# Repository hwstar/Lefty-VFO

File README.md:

# Lefty-VFO
Lefty Quad output VFO Motherboard

This is a 4 output VFO module for the lefty transceiver.

It uses 2 SI5351/MS5351 clock generator chips. 

There is a 4 channel PCA9546 I2C multiplexer on the board which is used to switch between the two SI5351's since they have a fixed device address.

Each SI5351 is driven from a common 26 MHz TCXO source using 74LVC1G04's as a buffer.

The SI5351's have dedicated ME6211 3.3V regulators to reduce cross coupling of spurs on the 3.3v power rails.

The VFO board used a Weact "Black Pill" STM32 MPU module. This module has 512kB of flash and 128kB of ram.

The display mounts on the front of the board using a 20 pin female socket header. The display used is a 3.3V 12864 monochrome display with SPI bus capability.

The vfo board is powered from 9-15V and uses a 12V to 5V switching power supply module with input PI filter to reduce the noise generated from the switcher module.

There is one 8 pin JST XH connector supplies 12V power and provides access to the I2C bus coming from one of the PCA9546 outputs.

The vfo board supports an optional 4x4 keypad, and an optical encoder.

There are 2 pin connector for the fan output. 

There are 2 pin connectors for the ptt, tune, and s-meter inputs.

There is a 6 pin connector for the UART in the Black pill.

There is an I2C EEPROM on the board to facilitate storing VFO configuration settings

The PCB design was done with KiCAD 6.0. The BOM files are in .csv format and are included in the top level directory. There is a combined BOM, and separate top and bottom SMT BOM's.

The firmware for the VFO is in a separate project located [here] (https://github.com/hwstar/FW_VFO_STM32_BLACK_PILL_ST7920) 

The gerber files are in the directory VFO_Rev_X2_Gerbers.

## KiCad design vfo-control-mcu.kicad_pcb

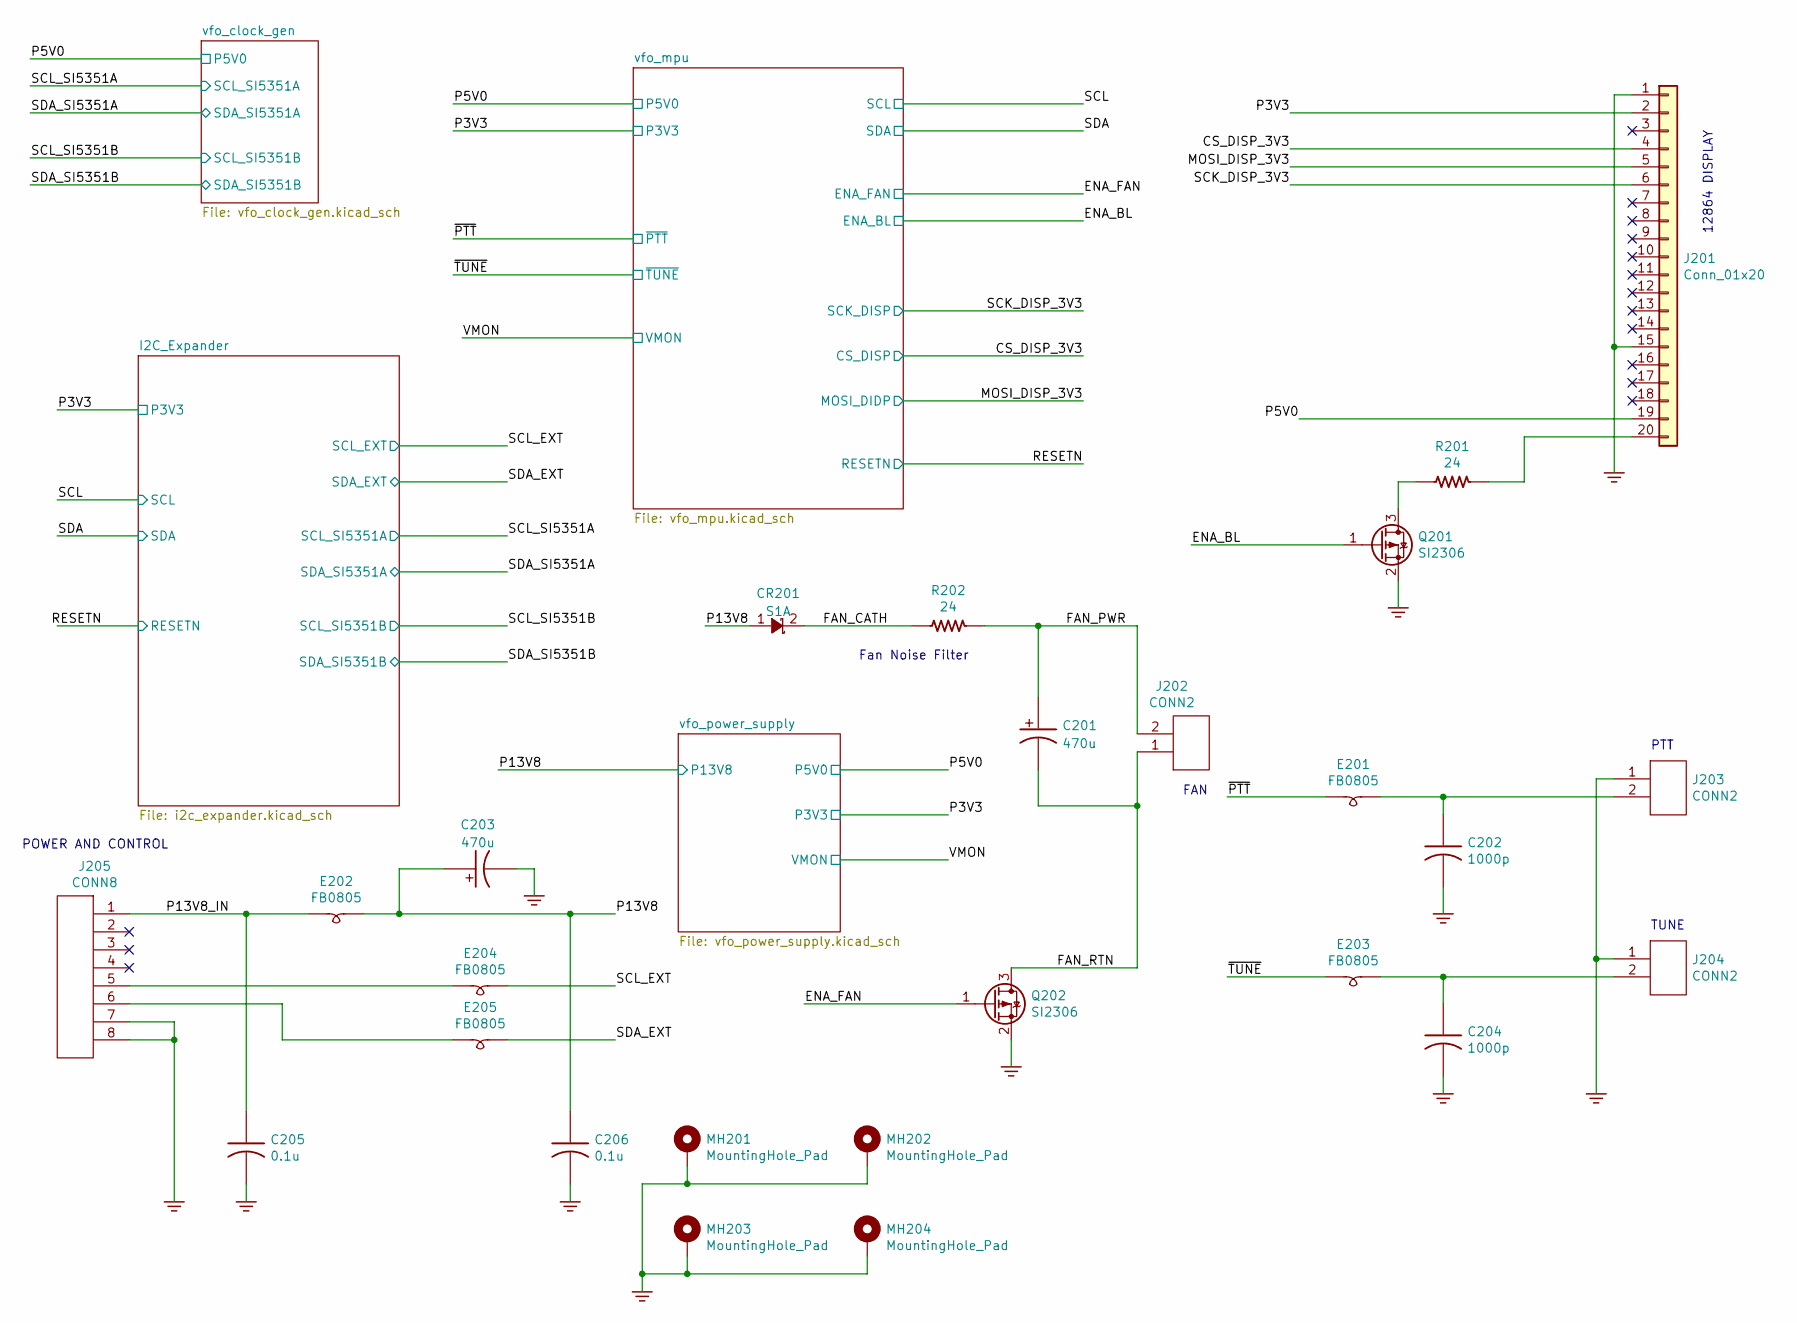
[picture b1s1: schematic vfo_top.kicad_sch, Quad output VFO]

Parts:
C201, C203: 470u; CP_Elec_10x10; PartNumber 800270-477
C202, C204: 1000p; C_0805_2012Metric_Pad1.18x1.45mm_HandSolder; PartNumber 800239-102
C205, C206: 0.1u; C_0805_2012Metric_Pad1.18x1.45mm_HandSolder; PartNumber 800238-104
CR201: S1A; SMA-SAR; PartNumber 800109-101
E201, E202, E203, E204, E205: FB0805; L_0805_2012Metric_Pad1.05x1.20mm_HandSolder; PartNumber 800245-601
J201: Conn_01x20; 12864_display; PartNumber 800283-020
J202, J203, J204: CONN2; JST_B2B_XH_A; PartNumber 800114-102
J205: CONN8; JST_B8B_XH_A; PartNumber 800114-108
MH201, MH202, MH203, MH204: MountingHole_Pad; MountingHole_3.2mm_M3_Pad_Via
Q201, Q202: SI2306; SOT-23; PartNumber 800123-101
R201, R202: 24; R_2512_6332Metric_Pad1.40x3.35mm_HandSolder; PartNumber 800248-240

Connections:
/vfo_top/CS_DISP_3V3: J201.4; also elsewhere on the board
/vfo_top/ENA_BL: Q201.1 (G); also elsewhere on the board
/vfo_top/ENA_FAN: Q202.1 (G); also elsewhere on the board
/vfo_top/FAN_CATH: CR201.2 (K), R202.2
/vfo_top/FAN_PWR: C201.1, J202.2, R202.1
/vfo_top/FAN_RTN: C201.2, J202.1, Q202.3 (D)
/vfo_top/MOSI_DISP_3V3: J201.5; also elsewhere on the board
/vfo_top/P3V3: J201.2; also elsewhere on the board
/vfo_top/P5V0: J201.19; also elsewhere on the board
/vfo_top/P13V8: C203.1, C206.1, CR201.1 (A), E202.2; also elsewhere on the board
/vfo_top/P13V8_IN: C205.1, E202.1, J205.1
/vfo_top/SCK_DISP_3V3: J201.6; also elsewhere on the board
/vfo_top/SCL_EXT: E204.2; also elsewhere on the board
/vfo_top/SDA_EXT: E205.2; also elsewhere on the board
/vfo_top/~PTT: E201.1; also elsewhere on the board
/vfo_top/~TUNE: E203.1; also elsewhere on the board
GND: C202.2, C203.2, C204.2, C205.2, C206.2, J201.1, J201.15, J203.1, J204.1, J205.7, J205.8, MH201.1, MH202.1, MH203.1, MH204.1, Q201.2 (S), Q202.2 (S); also elsewhere on the board
unnamed: C202.1, E201.2, J203.2
unnamed: C204.1, E203.2, J204.2
unnamed: E204.1, J205.5
unnamed: E205.1, J205.6
unnamed: J201.20, R201.1
unnamed: Q201.3 (D), R201.2

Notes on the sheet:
POWER AND CONTROL
PTT
TUNE
12864 DISPLAY
Fan Noise Filter
FAN

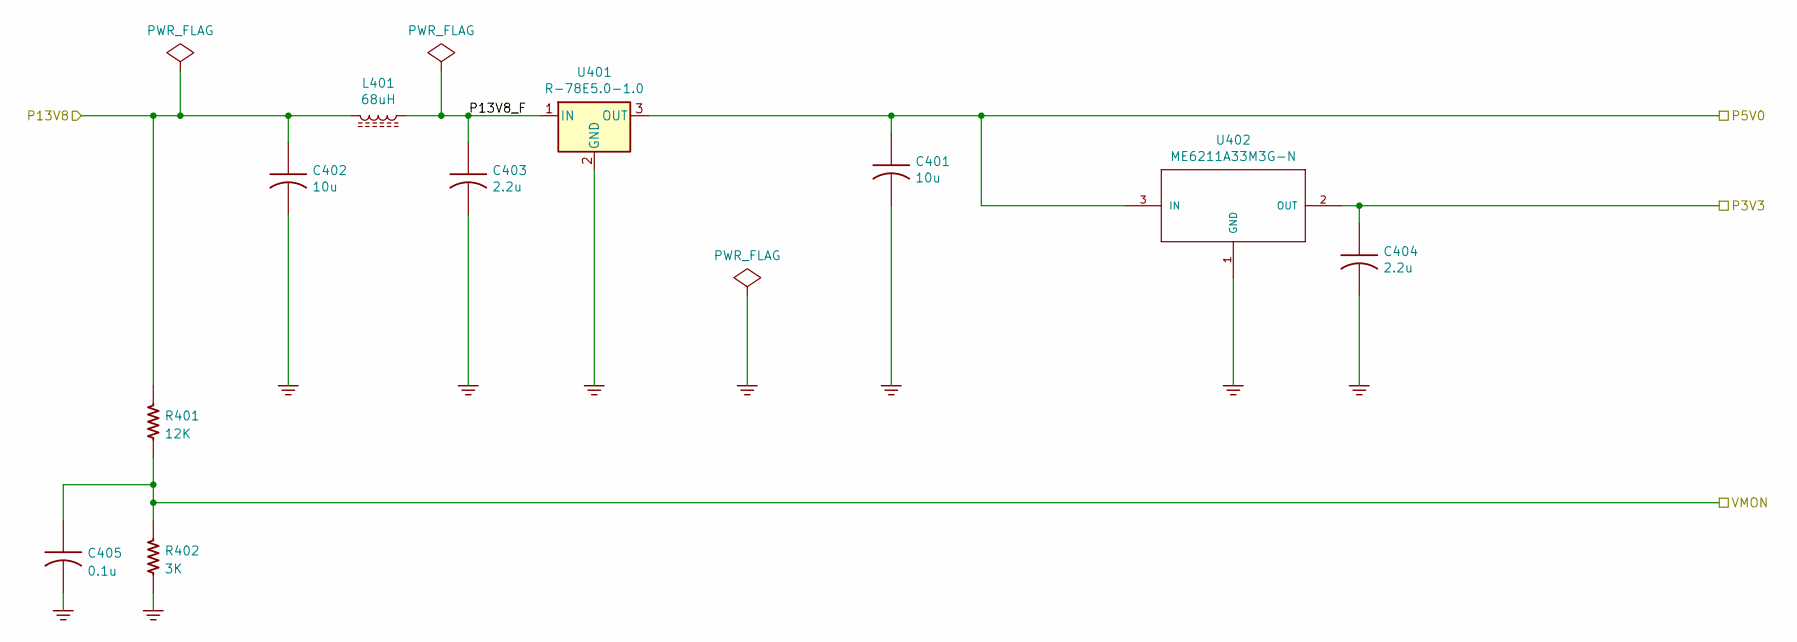
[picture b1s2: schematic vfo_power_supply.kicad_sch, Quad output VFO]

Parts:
C401, C402: 10u; C_0805_2012Metric_Pad1.18x1.45mm_HandSolder; PartNumber 800003-106
C403, C404: 2.2u; C_0805_2012Metric_Pad1.18x1.45mm_HandSolder; PartNumber 800003-225
C405: 0.1u; C_0805_2012Metric_Pad1.18x1.45mm_HandSolder; PartNumber 800238-104
L401: 68uH; IND-DRUM-7.8MMx5MM; PartNumber 800281-101
R401: 12K; R_0805_2012Metric_Pad1.20x1.40mm_HandSolder; PartNumber 800235-123
R402: 3K; R_0805_2012Metric_Pad1.20x1.40mm_HandSolder; PartNumber 800235-302
U401: R-78E5.0-1.0; RECom_R-78Ex.x-1.0; PartNumber 800201-500
U402: ME6211A33M3G-N; SOT23-3-SAR-V2; PartNumber 800187-101

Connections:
/vfo_top/P3V3: C404.1, U402.2 (OUT); also elsewhere on the board
/vfo_top/P5V0: C401.1, U401.3 (OUT), U402.3 (IN); also elsewhere on the board
/vfo_top/P13V8: C402.1, L401.2, R401.1; also elsewhere on the board
/vfo_top/VMON: C405.1, R401.2, R402.1; also elsewhere on the board
/vfo_top/vfo_power_supply/P13V8_F: C403.1, L401.1, U401.1 (IN)
GND: C401.2, C402.2, C403.2, C404.2, C405.2, R402.2, U401.2 (GND), U402.1 (GND); also elsewhere on the board

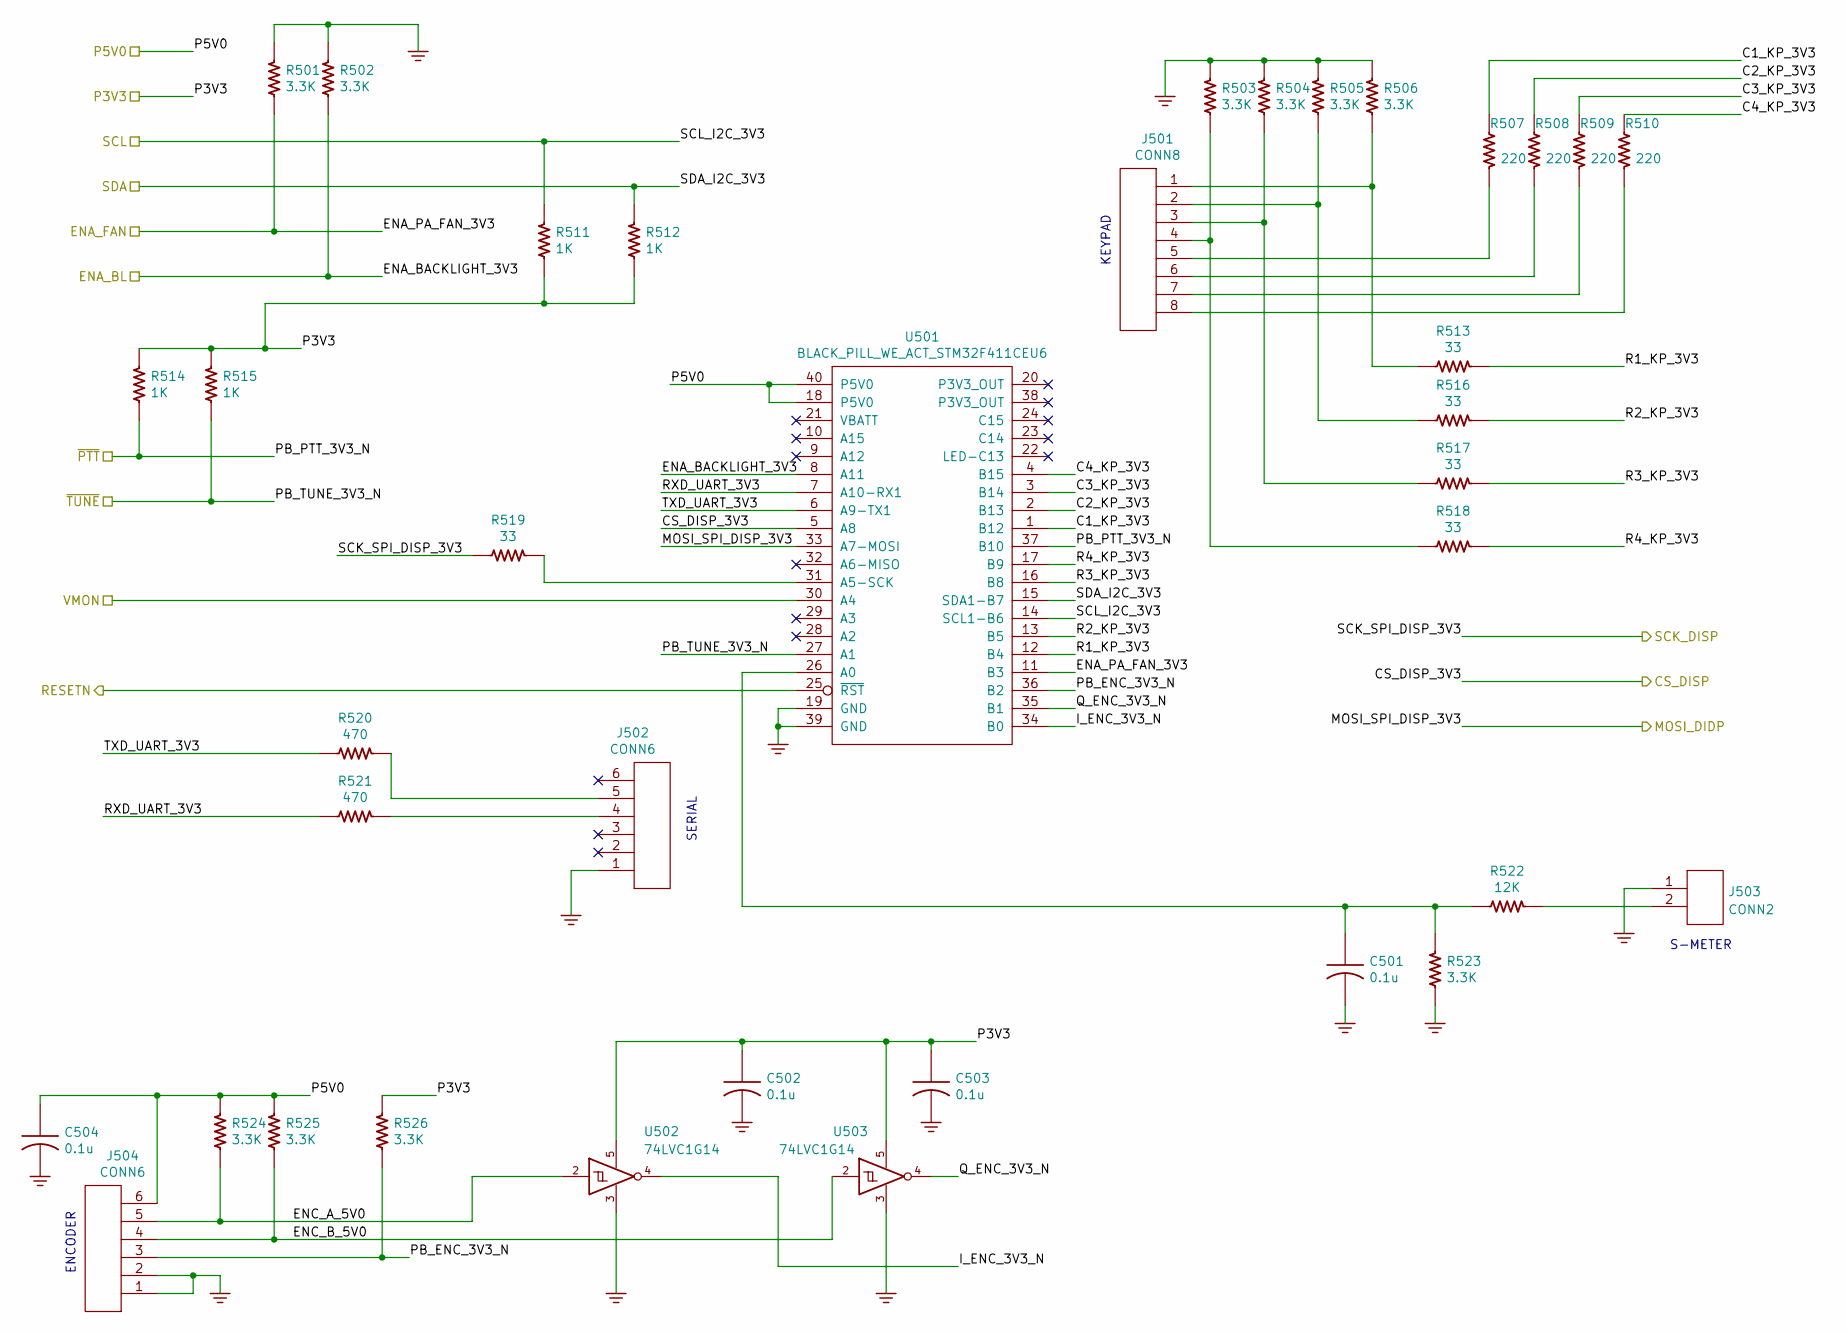
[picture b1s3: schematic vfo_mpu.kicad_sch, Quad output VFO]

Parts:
C501, C502, C503, C504: 0.1u; C_0805_2012Metric_Pad1.18x1.45mm_HandSolder; PartNumber 800238-104
J501: CONN8; JST_B8B_XH_A; PartNumber 800114-108
J502, J504: CONN6; JST_B6B_XH_A; PartNumber 800114-106
J503: CONN2; JST_B2B_XH_A; PartNumber 800114-102
R501, R502, R503, R504, R505, R506, R523, R524, R525, R526: 3.3K; R_0805_2012Metric_Pad1.20x1.40mm_HandSolder; PartNumber 800235-332
R507, R508, R509, R510: 220; R_0805_2012Metric_Pad1.20x1.40mm_HandSolder; PartNumber 800235-221
R511, R512, R514, R515: 1K; R_0805_2012Metric_Pad1.20x1.40mm_HandSolder; PartNumber 800235-102
R513, R516, R517, R518, R519: 33; R_0805_2012Metric_Pad1.20x1.40mm_HandSolder; PartNumber 800235-330
R520, R521: 470; R_0805_2012Metric_Pad1.20x1.40mm_HandSolder; PartNumber 800235-471
R522: 12K; R_0805_2012Metric_Pad1.20x1.40mm_HandSolder; PartNumber 800235-123
U501: BLACK_PILL_WE_ACT_STM32F411CEU6; BLACK_PILL_WE_ACT_STM32F411; PartNumber 800280-101
U502, U503: 74LVC1G14; SOT-23-5; PartNumber 800199-101

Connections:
/vfo_top/CS_DISP_3V3: U501.5 (A8); also elsewhere on the board
/vfo_top/ENA_BL: R502.2, U501.8 (A11); also elsewhere on the board
/vfo_top/ENA_FAN: R501.2, U501.11 (B3); also elsewhere on the board
/vfo_top/MOSI_DISP_3V3: U501.33 (A7-MOSI); also elsewhere on the board
/vfo_top/P3V3: C502.1, C503.1, R511.2, R512.2, R514.1, R515.1, R526.1, U502.5 (VCC), U503.5 (VCC); also elsewhere on the board
/vfo_top/P5V0: C504.1, J504.6, R524.1, R525.1, U501.18 (P5V0), U501.40 (P5V0); also elsewhere on the board
/vfo_top/RESETN: U501.25 (~RST); also elsewhere on the board
/vfo_top/SCK_DISP_3V3: R519.2; also elsewhere on the board
/vfo_top/SCL: R511.1, U501.14 (SCL1-B6); also elsewhere on the board
/vfo_top/SDA: R512.1, U501.15 (SDA1-B7); also elsewhere on the board
/vfo_top/VMON: U501.30 (A4); also elsewhere on the board
/vfo_top/vfo_mpu/C1_KP_3V3: R507.2, U501.1 (B12)
/vfo_top/vfo_mpu/C2_KP_3V3: R508.2, U501.2 (B13)
/vfo_top/vfo_mpu/C3_KP_3V3: R509.2, U501.3 (B14)
/vfo_top/vfo_mpu/C4_KP_3V3: R510.2, U501.4 (B15)
/vfo_top/vfo_mpu/ENC_A_5V0: J504.5, R524.2, U502.2
/vfo_top/vfo_mpu/ENC_B_5V0: J504.4, R525.2, U503.2
/vfo_top/vfo_mpu/I_ENC_3V3_N: U501.34 (B0), U502.4
/vfo_top/vfo_mpu/PB_ENC_3V3_N: J504.3, R526.2, U501.36 (B2)
/vfo_top/vfo_mpu/Q_ENC_3V3_N: U501.35 (B1), U503.4
/vfo_top/vfo_mpu/R1_KP_3V3: R513.1, U501.12 (B4)
/vfo_top/vfo_mpu/R2_KP_3V3: R516.1, U501.13 (B5)
/vfo_top/vfo_mpu/R3_KP_3V3: R517.1, U501.16 (B8)
/vfo_top/vfo_mpu/R4_KP_3V3: R518.1, U501.17 (B9)
/vfo_top/vfo_mpu/RXD_UART_3V3: R521.2, U501.7 (A10-RX1)
/vfo_top/vfo_mpu/TXD_UART_3V3: R520.2, U501.6 (A9-TX1)
/vfo_top/~PTT: R514.2, U501.37 (B10); also elsewhere on the board
/vfo_top/~TUNE: R515.2, U501.27 (A1); also elsewhere on the board
GND: C501.2, C502.2, C503.2, C504.2, J502.1, J503.1, J504.1, J504.2, R501.1, R502.1, R503.1, R504.1, R505.1, R506.1, R523.2, U501.19 (GND), U501.39 (GND), U502.3 (GND), U503.3 (GND); also elsewhere on the board
unnamed: C501.1, R522.2, R523.1, U501.26 (A0)
unnamed: J501.1, R506.2, R513.2
unnamed: J501.2, R505.2, R516.2
unnamed: J501.3, R504.2, R517.2
unnamed: J501.4, R503.2, R518.2
unnamed: J501.5, R507.1
unnamed: J501.6, R508.1
unnamed: J501.7, R509.1
unnamed: J501.8, R510.1
unnamed: J502.4, R521.1
unnamed: J502.5, R520.1
unnamed: J503.2, R522.1
unnamed: R519.1, U501.31 (A5-SCK)

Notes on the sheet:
KEYPAD
ENCODER
SERIAL
S-METER

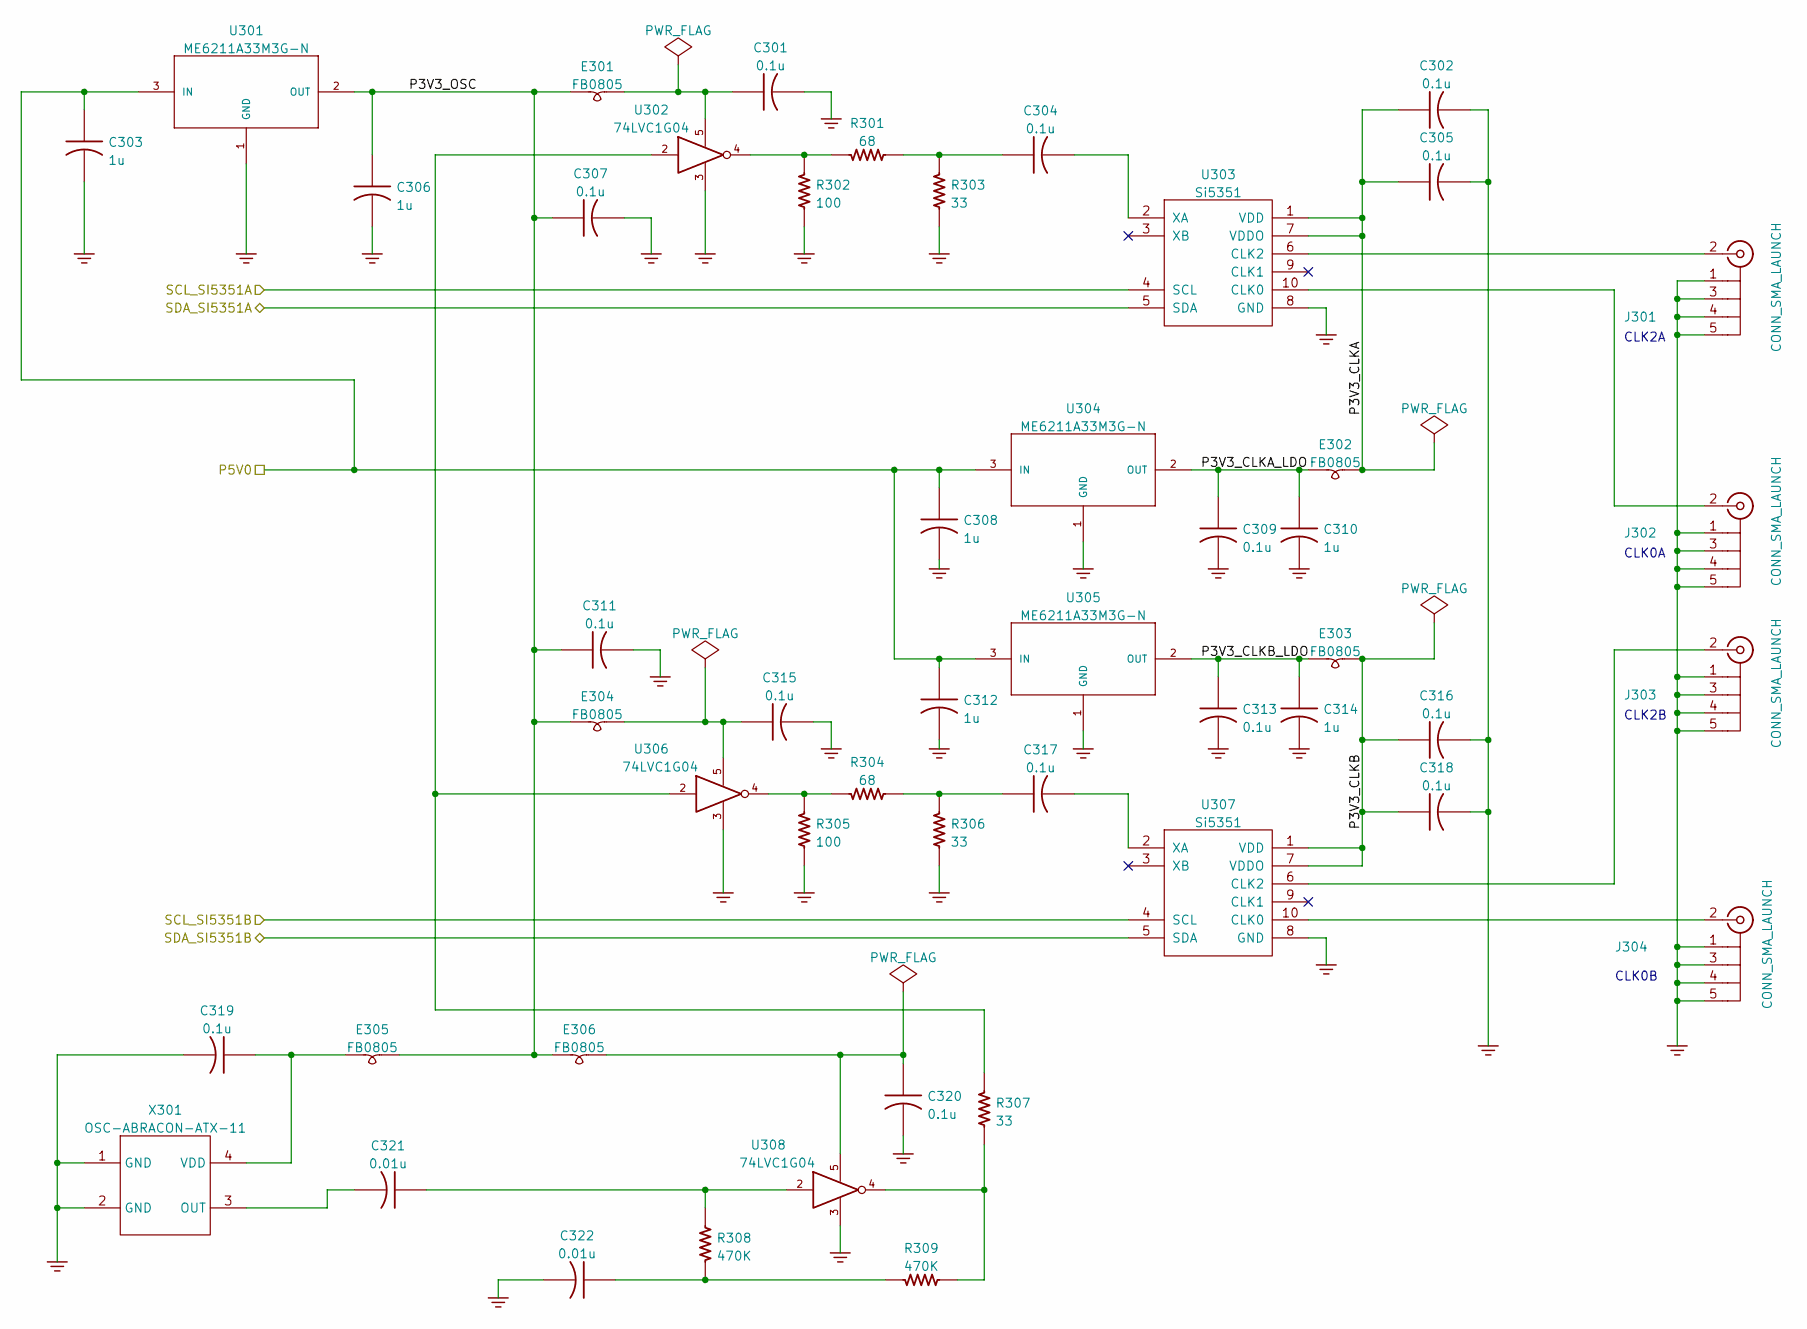
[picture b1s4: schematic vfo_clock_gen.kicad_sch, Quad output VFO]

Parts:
C301, C302, C304, C305, C307, C309, C311, C313, C315, C316, C317, C318, C319, C320: 0.1u; C_0603_1608Metric_Pad1.08x0.95mm_HandSolder; PartNumber 800063-104
C303, C306, C308, C310, C312, C314: 1u; C_0805_2012Metric_Pad1.18x1.45mm_HandSolder; PartNumber 800238-105
C321, C322: 0.01u; C_0805_2012Metric_Pad1.18x1.45mm_HandSolder; PartNumber 800238-103
E301, E302, E303, E304, E305, E306: FB0805; L_0805_2012Metric_Pad1.05x1.20mm_HandSolder; PartNumber 800245-601
J301, J302, J303, J304: CONN_SMA_LAUNCH; SMA_Launch_Kinghelm_KH-SMA-KE8-G; PartNumber 800233-101
R301, R304: 68; R_0805_2012Metric_Pad1.20x1.40mm_HandSolder; PartNumber 800235-680
R302, R305: 100; R_0805_2012Metric_Pad1.20x1.40mm_HandSolder; PartNumber 800235-101
R303, R306, R307: 33; R_0805_2012Metric_Pad1.20x1.40mm_HandSolder; PartNumber 800235-330
R308, R309: 470K; R_0805_2012Metric_Pad1.20x1.40mm_HandSolder; PartNumber 800235-474
U301, U304, U305: ME6211A33M3G-N; SOT23-3-SAR-V2; PartNumber 800187-101
U302, U306, U308: 74LVC1G04; SOT-23-5; PartNumber 800289-101
U303, U307: Si5351; MSOP-10-SAR; PartNumber 800288-101
X301: OSC-ABRACON-ATX-11; Oscillator_SMD_Abracon_ASE-4Pin_3.2x2.5mm_HandSoldering; PartNumber 800291-256

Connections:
/vfo_top/P5V0: C303.1, C308.1, C312.1, U301.3 (IN), U304.3 (IN), U305.3 (IN); also elsewhere on the board
/vfo_top/SCL_SI5351A: U303.4 (SCL); also elsewhere on the board
/vfo_top/SCL_SI5351B: U307.4 (SCL); also elsewhere on the board
/vfo_top/SDA_SI5351A: U303.5 (SDA); also elsewhere on the board
/vfo_top/SDA_SI5351B: U307.5 (SDA); also elsewhere on the board
/vfo_top/vfo_clock_gen/P3V3_CLKA: C302.1, C305.1, E302.2, U303.1 (VDD), U303.7 (VDDO)
/vfo_top/vfo_clock_gen/P3V3_CLKA_LDO: C309.1, C310.1, E302.1, U304.2 (OUT)
/vfo_top/vfo_clock_gen/P3V3_CLKB: C316.1, C318.1, E303.2, U307.1 (VDD), U307.7 (VDDO)
/vfo_top/vfo_clock_gen/P3V3_CLKB_LDO: C313.1, C314.1, E303.1, U305.2 (OUT)
/vfo_top/vfo_clock_gen/P3V3_OSC: C306.1, C307.1, C311.1, E301.1, E304.1, E305.2, E306.1, U301.2 (OUT)
GND: C301.2, C302.2, C303.2, C305.2, C306.2, C307.2, C308.2, C309.2, C310.2, C311.2, C312.2, C313.2, C314.2, C315.2, C316.2, C318.2, C319.2, C320.2, C322.2, J301.1, J301.3, J301.4, J301.5, J302.1, J302.3, J302.4, J302.5, J303.1, J303.3, J303.4, J303.5, J304.1, J304.3, J304.4, J304.5, R302.2, R303.2, R305.2, R306.2, U301.1 (GND), U302.3 (GND), U303.8 (GND), U304.1 (GND), U305.1 (GND), U306.3 (GND), U307.8 (GND), U308.3 (GND), X301.1 (GND), X301.2 (GND); also elsewhere on the board
unnamed: C301.1, E301.2, U302.5 (VCC)
unnamed: C304.1, R301.2, R303.1
unnamed: C304.2, U303.2 (XA)
unnamed: C315.1, E304.2, U306.5 (VCC)
unnamed: C317.1, R304.2, R306.1
unnamed: C317.2, U307.2 (XA)
unnamed: C319.1, E305.1, X301.4 (VDD)
unnamed: C320.1, E306.2, U308.5 (VCC)
unnamed: C321.1, R308.2, U308.2
unnamed: C321.2, X301.3 (OUT)
unnamed: C322.1, R308.1, R309.1
unnamed: J301.2, U303.6 (CLK2)
unnamed: J302.2, U303.10 (CLK0)
unnamed: J303.2, U307.6 (CLK2)
unnamed: J304.2, U307.10 (CLK0)
unnamed: R301.1, R302.1, U302.4
unnamed: R304.1, R305.1, U306.4
unnamed: R307.1, U302.2, U306.2
unnamed: R307.2, R309.2, U308.4

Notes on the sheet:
CLK0B
CLK0A
CLK2A
CLK2B

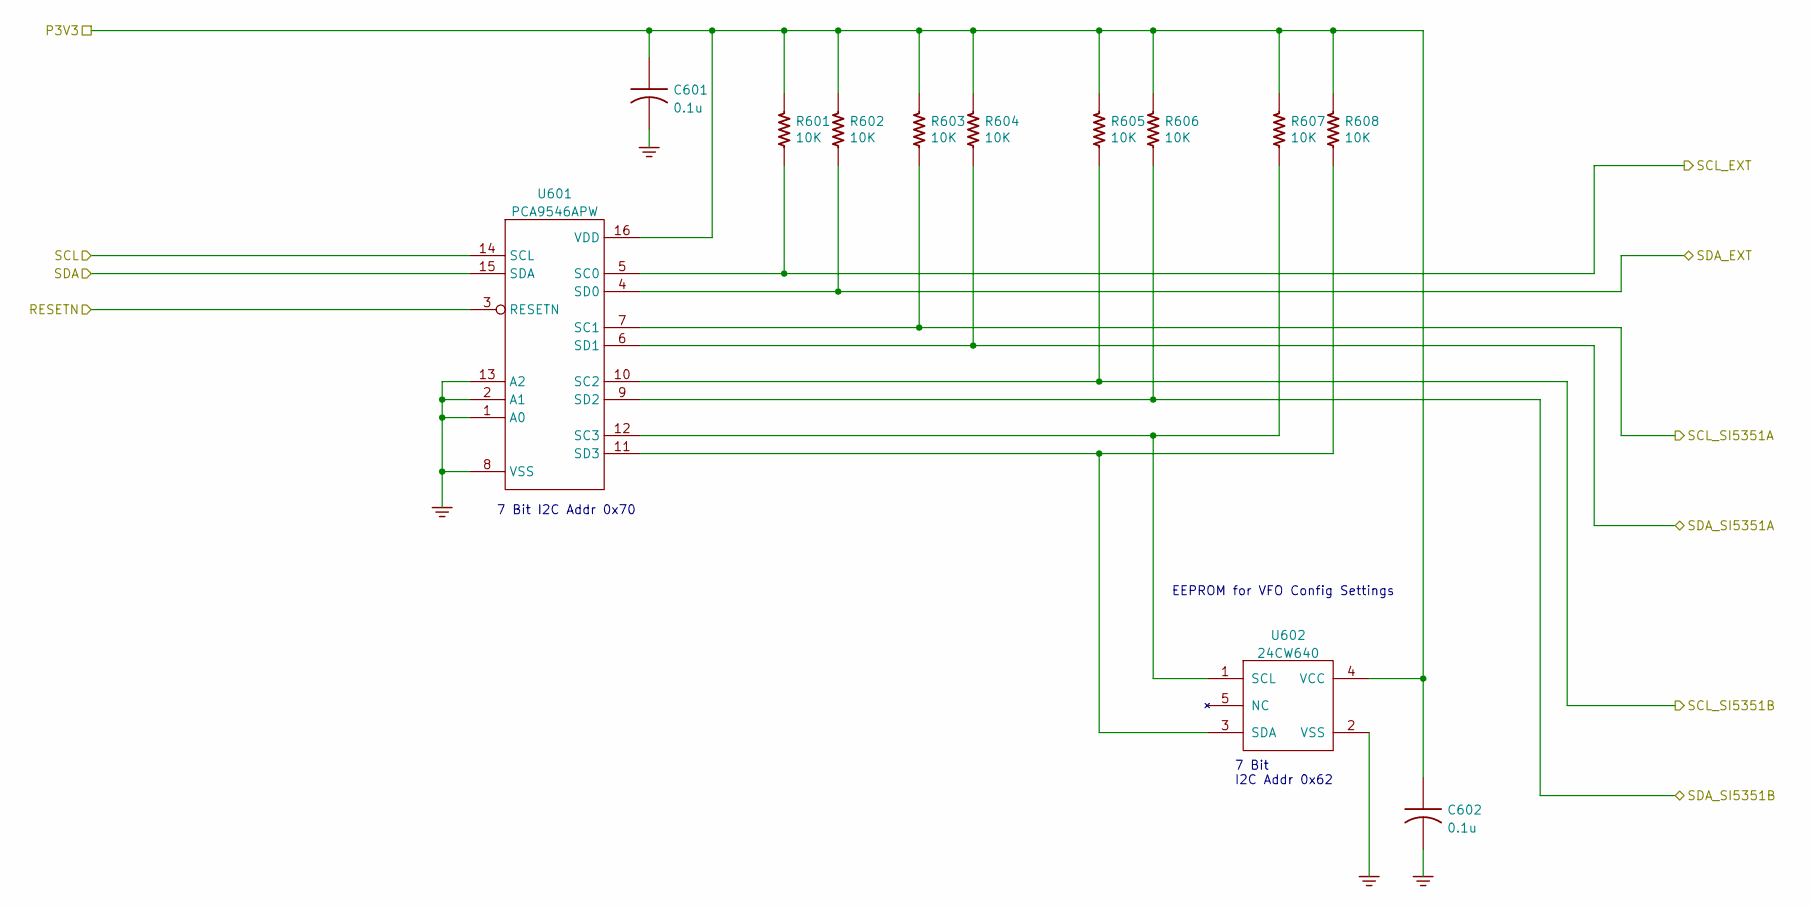
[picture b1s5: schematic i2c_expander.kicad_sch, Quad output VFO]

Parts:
C601, C602: 0.1u; C_0603_1608Metric_Pad1.08x0.95mm_HandSolder; PartNumber 800063-104
R601, R602, R603, R604, R605, R606, R607, R608: 10K; R_0805_2012Metric_Pad1.20x1.40mm_HandSolder; PartNumber 800235-103
U601: PCA9546APW; TSSOP-16_4.4x5mm_P0.65mm; PartNumber 800290-101
U602: 24CW640; SOT23-5-SAR; PartNumber 800284-101

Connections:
/vfo_top/P3V3: C601.1, C602.1, R601.1, R602.1, R603.1, R604.1, R605.1, R606.1, R607.1, R608.1, U601.16 (VDD), U602.4 (VCC); also elsewhere on the board
/vfo_top/RESETN: U601.3 (RESETN); also elsewhere on the board
/vfo_top/SCL: U601.14 (SCL); also elsewhere on the board
/vfo_top/SCL_EXT: R601.2, U601.5 (SC0); also elsewhere on the board
/vfo_top/SCL_SI5351A: R603.2, U601.7 (SC1); also elsewhere on the board
/vfo_top/SCL_SI5351B: R605.2, U601.10 (SC2); also elsewhere on the board
/vfo_top/SDA: U601.15 (SDA); also elsewhere on the board
/vfo_top/SDA_EXT: R602.2, U601.4 (SD0); also elsewhere on the board
/vfo_top/SDA_SI5351A: R604.2, U601.6 (SD1); also elsewhere on the board
/vfo_top/SDA_SI5351B: R606.2, U601.9 (SD2); also elsewhere on the board
GND: C601.2, C602.2, U601.1 (A0), U601.2 (A1), U601.8 (VSS), U601.13 (A2), U602.2 (VSS); also elsewhere on the board
unnamed: R607.2, U601.12 (SC3), U602.1 (SCL)
unnamed: R608.2, U601.11 (SD3), U602.3 (SDA)

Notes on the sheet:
EEPROM for VFO Config Settings
7 Bit I2C Addr 0x62
7 Bit I2C Addr 0x70

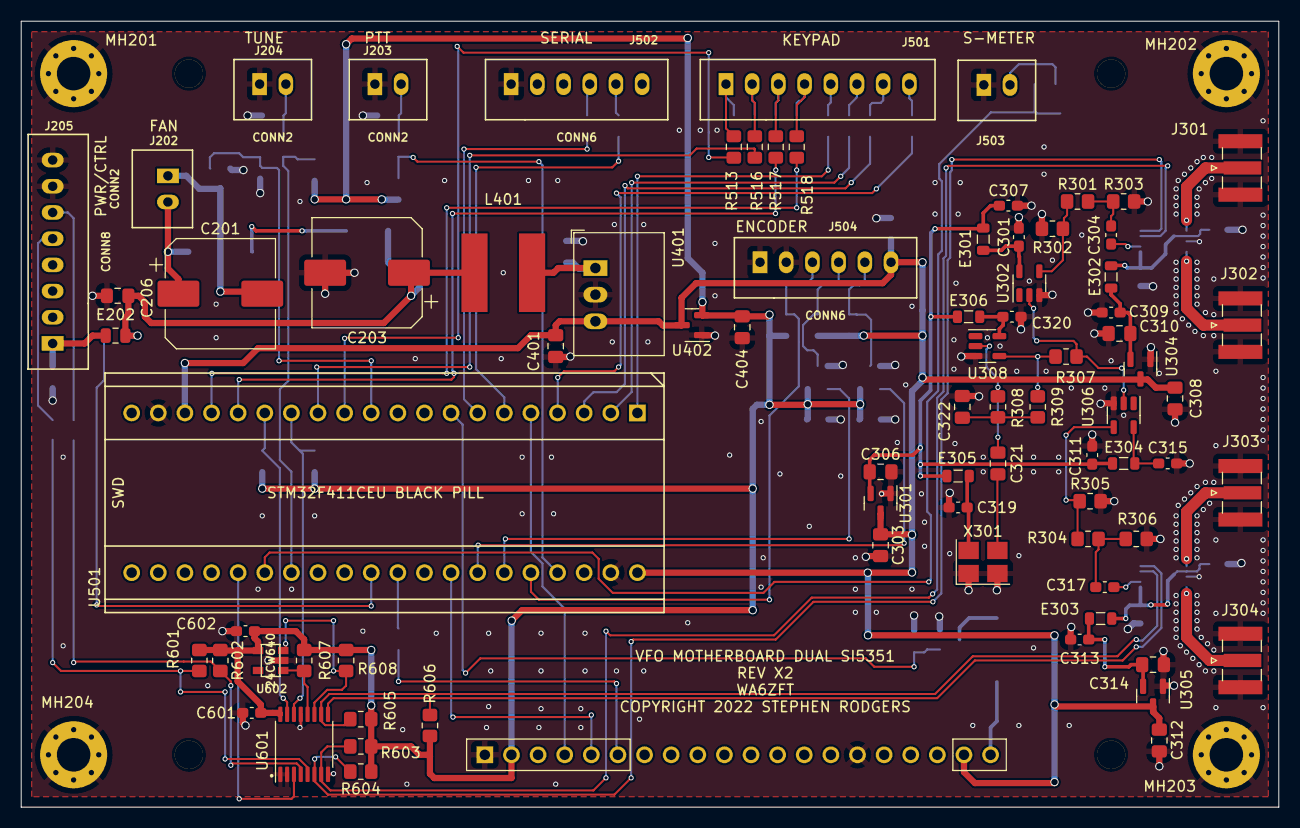
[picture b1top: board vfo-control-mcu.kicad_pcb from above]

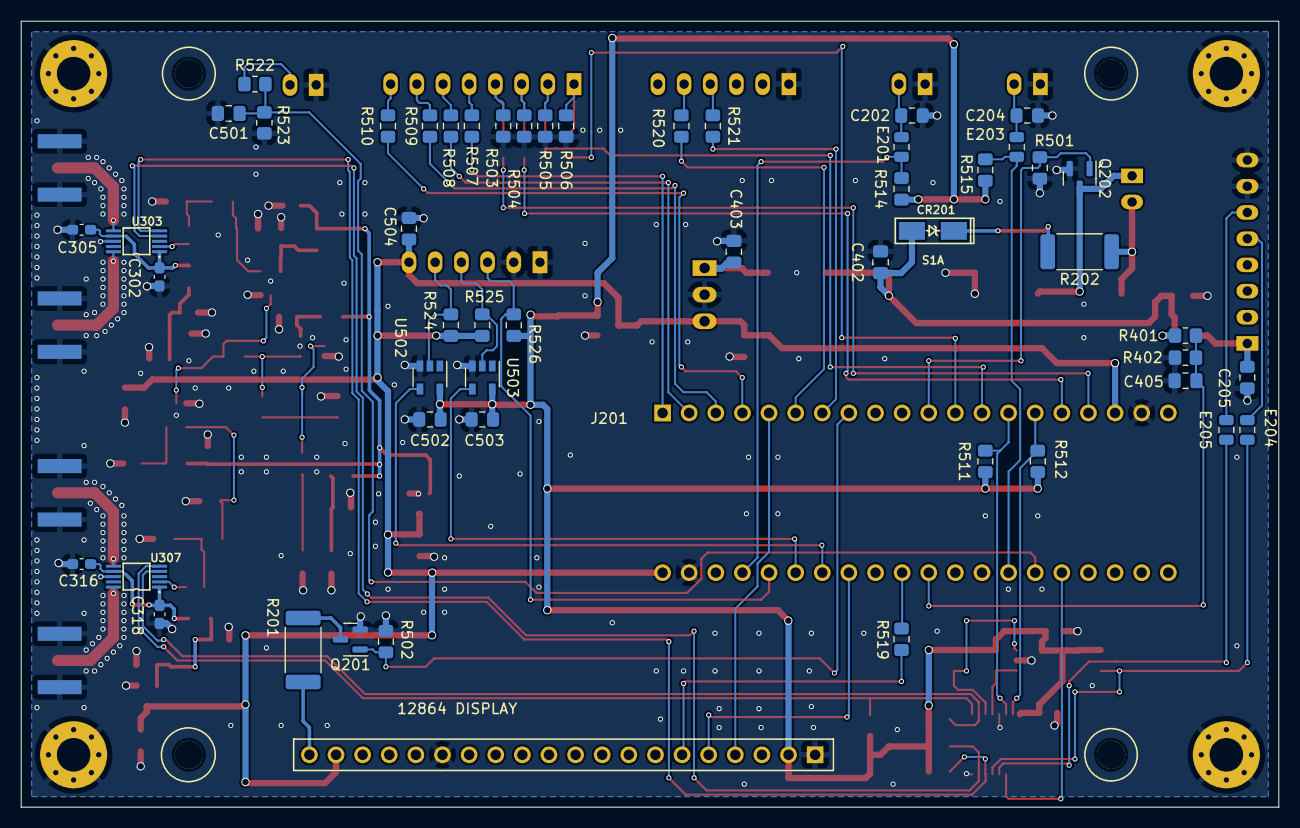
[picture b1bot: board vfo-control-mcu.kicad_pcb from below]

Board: 2 copper layers, 120.0 x 75.0 mm, 134 parts (52 on the bottom side), 86 nets.

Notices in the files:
vfo-control-mcu.kicad_pcb:
COPYRIGHT 2022 STEPHEN RODGERS
